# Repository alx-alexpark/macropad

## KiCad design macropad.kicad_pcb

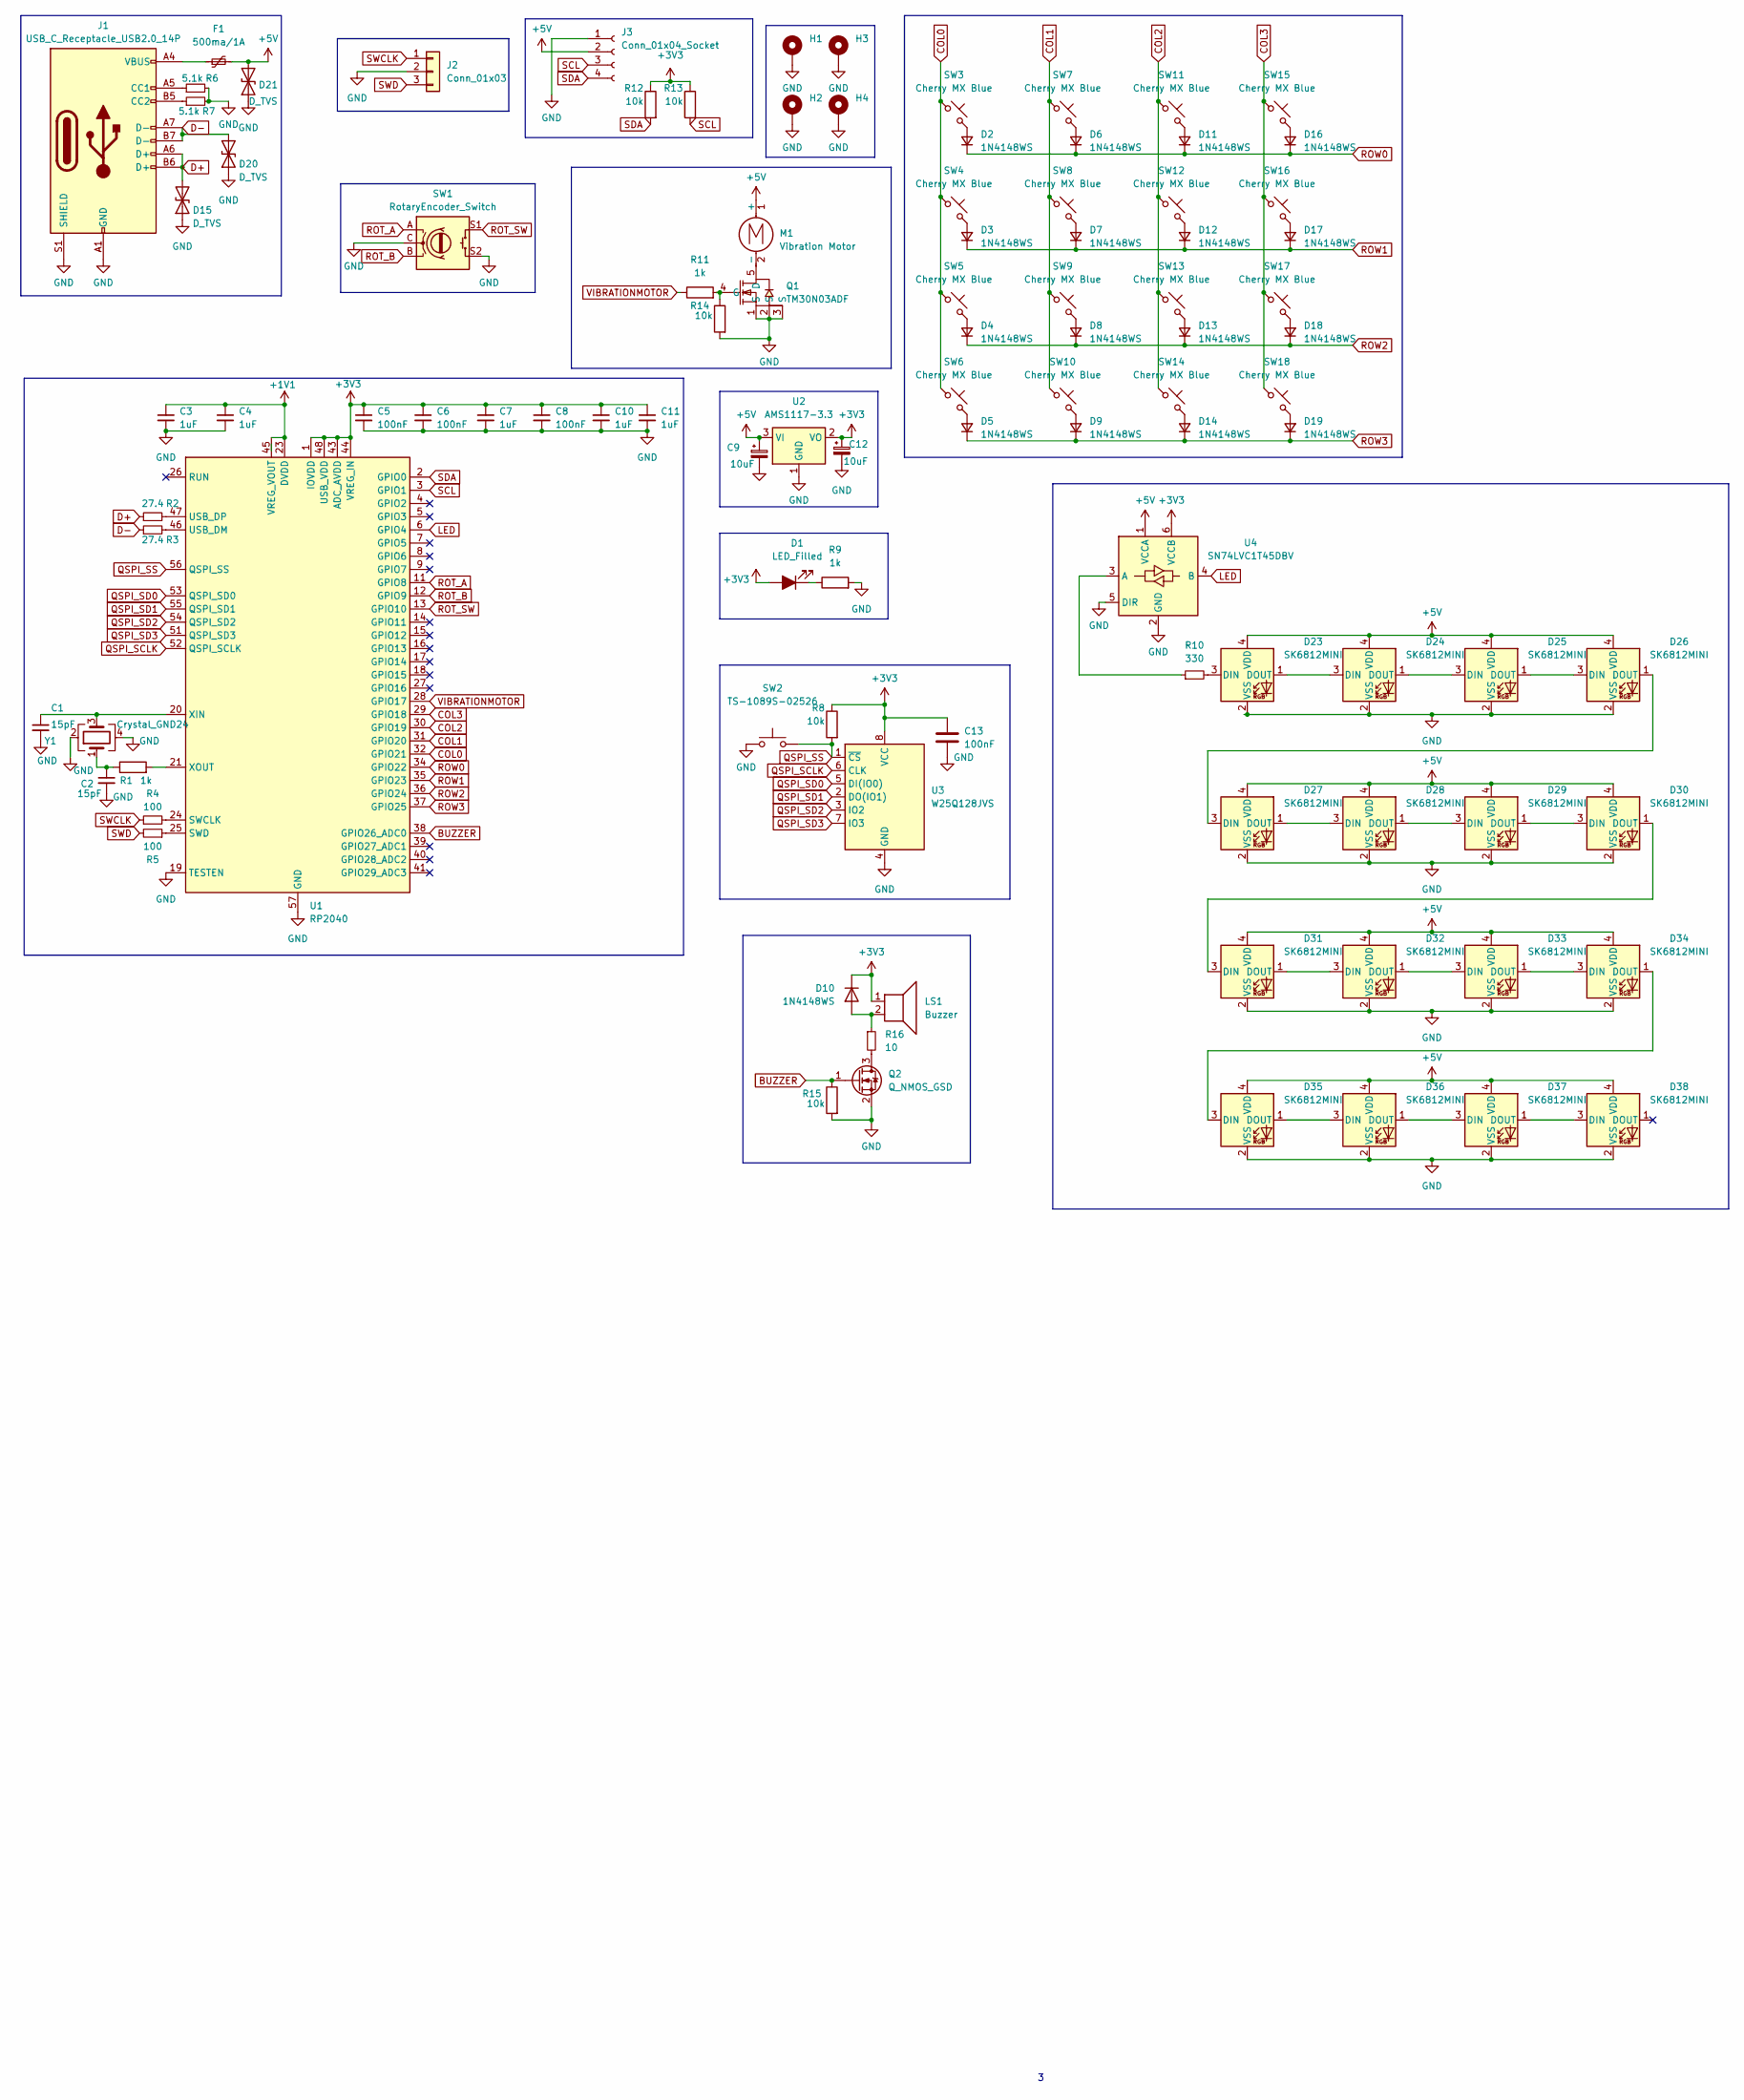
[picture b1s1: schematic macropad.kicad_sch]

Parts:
C1, C2: 15pF; C_0402_1005Metric; LCSC Part C1548
C3, C4, C7, C10, C11: 1uF; C_0402_1005Metric; LCSC Part C52923
C5, C6, C8, C13: 100nF; C_0402_1005Metric; LCSC Part C1525
C9, C12: 10uF; C_1206_3216Metric; LCSC Part C7171
D1: LED_Filled; LED_0603_1608Metric; LCSC Part C2286
D2, D3, D4, D5, D6, D7, D8, D9, D11, D12, D13, D14, D16, D17, D18, D19: 1N4148WS; D_SOD-323F; LCSC Part C917117
D10: 1N4148WS; D_SOD-323; LCSC Part C2828422
D15, D20, D21: D_TVS; D_SOD-923; LCSC Part C96512
D23, D24, D25, D26, D27, D28, D29, D30, D31, D32, D33, D34, D35, D36, D37, D38: SK6812MINI; SK6812MINI-E; LCSC Part C5149201
F1: 500ma/1A; Fuse_1206_3216Metric_Pad1.42x1.75mm_HandSolder; LCSC Part C720075
H1, H2, H3, H4: MountingHole_Pad; MountingHole_2.2mm_M2_DIN965_Pad
J1: USB_C_Receptacle_USB2.0_14P; USB_C_Receptacle_G-Switch_GT-USB-7010ASV; LCSC Part C2988369
J2: Conn_01x03; JST_SH_BM03B-SRSS-TB_1x03-1MP_P1.00mm_Vertical; LCSC Part C160389
J3: Conn_01x04_Socket; OLED-TH_L38.0-W12.0_HS91L02W2C01; LCSC Part C5248081
LS1: Buzzer; BUZ-SMD_4P-L8.5-W8.5-P8.50-BR; LCSC Part C94599
M1: Vibration Motor; PinHeader_1x02_P2.54mm_Vertical
Q1: TM30N03ADF; WDFN-5_L3.3-W3.3-P0.65-BL; LCSC Part C7422839
Q2: Q_NMOS_GSD; SOT-23_Handsoldering; LCSC Part C347475
R1, R9, R11: 1k; R_0402_1005Metric; LCSC Part C11702
R2, R3: 27.4; R_0603_1608Metric; LCSC Part C5126244
R4, R5: 100; R_0603_1608Metric_Pad0.98x0.95mm_HandSolder; LCSC Part C7250
R6, R7: 5.1k; R_0603_1608Metric_Pad0.98x0.95mm_HandSolder; LCSC Part C23186
R8, R12, R13, R14, R15: 10k; R_0805_2012Metric; LCSC Part C17414
R10: 330; R_0603_1608Metric_Pad0.98x0.95mm_HandSolder; LCSC Part C23138
R16: 10; R_0603_1608Metric_Pad0.98x0.95mm_HandSolder; LCSC Part C22859
SW1: RotaryEncoder_Switch; SW-TH_EC11XXXXXXXX; LCSC Part C470742
SW2: TS-1089S-02526; SW-SMD_4P-L4.2-W3.3-P2.15-LS5.1; LCSC Part C455282
SW3, SW4, SW5, SW6, SW7, SW8, SW9, SW10, SW11, SW12, SW13, SW14, SW15, SW16, SW17, SW18: Cherry MX Blue; SW_Cherry_MX_PCB_1.00u
U1: RP2040; QFN-56-1EP_7x7mm_P0.4mm_EP3.2x3.2mm; LCSC Part C2040
U2: AMS1117-3.3; SOT-223-3_TabPin2; LCSC Part C6186
U3: W25Q128JVS; SOIC-8_5.23x5.23mm_P1.27mm; LCSC Part C97521
U4: SN74LVC1T45DBV; SOT-23-6; LCSC Part C7843
Y1: Crystal_GND24; Crystal_SMD_3225-4Pin_3.2x2.5mm; LCSC Part C20625731

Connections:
+1V1: C3.1, C4.1, U1.23 (DVDD), U1.45 (VREG_VOUT), U1.50 (DVDD)
+3V3: C5.1, C6.1, C7.1, C8.1, C10.1, C11.1, C12.1, C13.1, D1.2 (A), D10.1 (K), LS1.1, R8.1, R12.1, R13.1, U1.1 (IOVDD), U1.10 (IOVDD), U1.22 (IOVDD), U1.33 (IOVDD), U1.42 (IOVDD), U1.43 (ADC_AVDD), U1.44 (VREG_IN), U1.48 (USB_VDD), U1.49 (IOVDD), U2.2 (VO), U3.8 (VCC), U4.6 (VCCB)
+5V: C9.1, D21.2 (A2), D23.4 (VDD), D24.4 (VDD), D25.4 (VDD), D26.4 (VDD), D27.4 (VDD), D28.4 (VDD), D29.4 (VDD), D30.4 (VDD), D31.4 (VDD), D32.4 (VDD), D33.4 (VDD), D34.4 (VDD), D35.4 (VDD), D36.4 (VDD), D37.4 (VDD), D38.4 (VDD), F1.2, J3.2, M1.1 (+), U2.3 (VI), U4.1 (VCCA)
BUZZER: Q2.1 (G), R15.1, U1.38 (GPIO26_ADC0)
COL0: SW3.1, SW4.1, SW5.1, SW6.1, U1.32 (GPIO21)
COL1: SW7.1, SW8.1, SW9.1, SW10.1, U1.31 (GPIO20)
COL2: SW11.1, SW12.1, SW13.1, SW14.1, U1.30 (GPIO19)
COL3: SW15.1, SW16.1, SW17.1, SW18.1, U1.29 (GPIO18)
D+: D15.2 (A2), J1.A6 (D+), J1.B6 (D+), R2.1
D-: D20.2 (A2), J1.A7 (D-), J1.B7 (D-), R3.1
GND: C1.2, C2.2, C3.2, C4.2, C5.2, C6.2, C7.2, C8.2, C9.2, C10.2, C11.2, C12.2, C13.2, D15.1 (A1), D20.1 (A1), D21.1 (A1), D23.2 (VSS), D24.2 (VSS), D25.2 (VSS), D26.2 (VSS), D27.2 (VSS), D28.2 (VSS), D29.2 (VSS), D30.2 (VSS), D31.2 (VSS), D32.2 (VSS), D33.2 (VSS), D34.2 (VSS), D35.2 (VSS), D36.2 (VSS), D37.2 (VSS), D38.2 (VSS), H1.1, H2.1, H3.1, H4.1, J1.A1 (GND), J1.A12 (GND), J1.B1 (GND), J1.B12 (GND), J1.S1 (SHIELD), J2.2, J3.1, Q1.1 (S), Q1.2 (S), Q1.3 (S), Q2.2 (S), R6.2, R7.2, R9.2, R14.2, R15.2, SW1.C, SW1.S2, SW2.1, U1.19 (TESTEN), U1.57 (GND), U2.1 (GND), U3.4 (GND), U4.2 (GND), U4.5 (DIR), Y1.2, Y1.4
LED: U1.6 (GPIO4), U4.4 (B)
unnamed: C2.1, R1.1, Y1.1
unnamed: D1.1 (K), R9.1
unnamed: D2.2 (A), SW3.2
unnamed: D3.2 (A), SW4.2
unnamed: D4.2 (A), SW5.2
unnamed: D5.2 (A), SW6.2
unnamed: D6.2 (A), SW7.2
unnamed: D7.2 (A), SW8.2
unnamed: D8.2 (A), SW9.2
unnamed: D9.2 (A), SW10.2
unnamed: D10.2 (A), LS1.2, R16.1
unnamed: D11.2 (A), SW11.2
unnamed: D12.2 (A), SW12.2
unnamed: D13.2 (A), SW13.2
unnamed: D14.2 (A), SW14.2
unnamed: D16.2 (A), SW15.2
unnamed: D17.2 (A), SW16.2
unnamed: D18.2 (A), SW17.2
unnamed: D19.2 (A), SW18.2
unnamed: D23.3 (DIN), R10.2
unnamed: D23.1 (DOUT), D24.3 (DIN)
unnamed: D24.1 (DOUT), D25.3 (DIN)
unnamed: D25.1 (DOUT), D26.3 (DIN)
unnamed: D26.1 (DOUT), D27.3 (DIN)
unnamed: D27.1 (DOUT), D28.3 (DIN)
unnamed: D28.1 (DOUT), D29.3 (DIN)
unnamed: D29.1 (DOUT), D30.3 (DIN)
unnamed: D30.1 (DOUT), D31.3 (DIN)
unnamed: D31.1 (DOUT), D32.3 (DIN)
unnamed: D32.1 (DOUT), D33.3 (DIN)
unnamed: D33.1 (DOUT), D34.3 (DIN)
unnamed: D34.1 (DOUT), D35.3 (DIN)
unnamed: D35.1 (DOUT), D36.3 (DIN)
unnamed: D36.1 (DOUT), D37.3 (DIN)
unnamed: D37.1 (DOUT), D38.3 (DIN)
unnamed: F1.1, J1.A4 (VBUS), J1.A9 (VBUS), J1.B4 (VBUS), J1.B9 (VBUS)
unnamed: J1.A5 (CC1), R6.1
unnamed: J1.B5 (CC2), R7.1
unnamed: M1.2 (-), Q1.5 (D)
unnamed: Q1.4 (G), R11.2, R14.1
unnamed: Q2.3 (D), R16.2
unnamed: R4.2, U1.24 (SWCLK)
unnamed: R5.1, U1.25 (SWD)
unnamed: R3.2, U1.46 (USB_DM)
unnamed: R2.2, U1.47 (USB_DP)
unnamed: C1.1, U1.20 (XIN), Y1.3
unnamed: R1.2, U1.21 (XOUT)
unnamed: R10.1, U4.3 (A)
QSPI_SCLK: U1.52 (QSPI_SCLK), U3.6 (CLK)
QSPI_SD0: U1.53 (QSPI_SD0), U3.5 (DI(IO0))
QSPI_SD1: U1.55 (QSPI_SD1), U3.2 (DO(IO1))
QSPI_SD2: U1.54 (QSPI_SD2), U3.3 (IO2)
QSPI_SD3: U1.51 (QSPI_SD3), U3.7 (IO3)
QSPI_SS: R8.2, SW2.2, U1.56 (QSPI_SS), U3.1 (~CS)
ROT_A: SW1.A, U1.11 (GPIO8)
ROT_B: SW1.B, U1.12 (GPIO9)
ROT_SW: SW1.S1, U1.13 (GPIO10)
ROW0: D2.1 (K), D6.1 (K), D11.1 (K), D16.1 (K), U1.34 (GPIO22)
ROW1: D3.1 (K), D7.1 (K), D12.1 (K), D17.1 (K), U1.35 (GPIO23)
ROW2: D4.1 (K), D8.1 (K), D13.1 (K), D18.1 (K), U1.36 (GPIO24)
ROW3: D5.1 (K), D9.1 (K), D14.1 (K), D19.1 (K), U1.37 (GPIO25)
SCL: J3.3, R13.2, U1.3 (GPIO1)
SDA: J3.4, R12.2, U1.2 (GPIO0)
SWCLK: J2.1, R4.1
SWD: J2.3, R5.2
VIBRATIONMOTOR: R11.1, U1.28 (GPIO17)

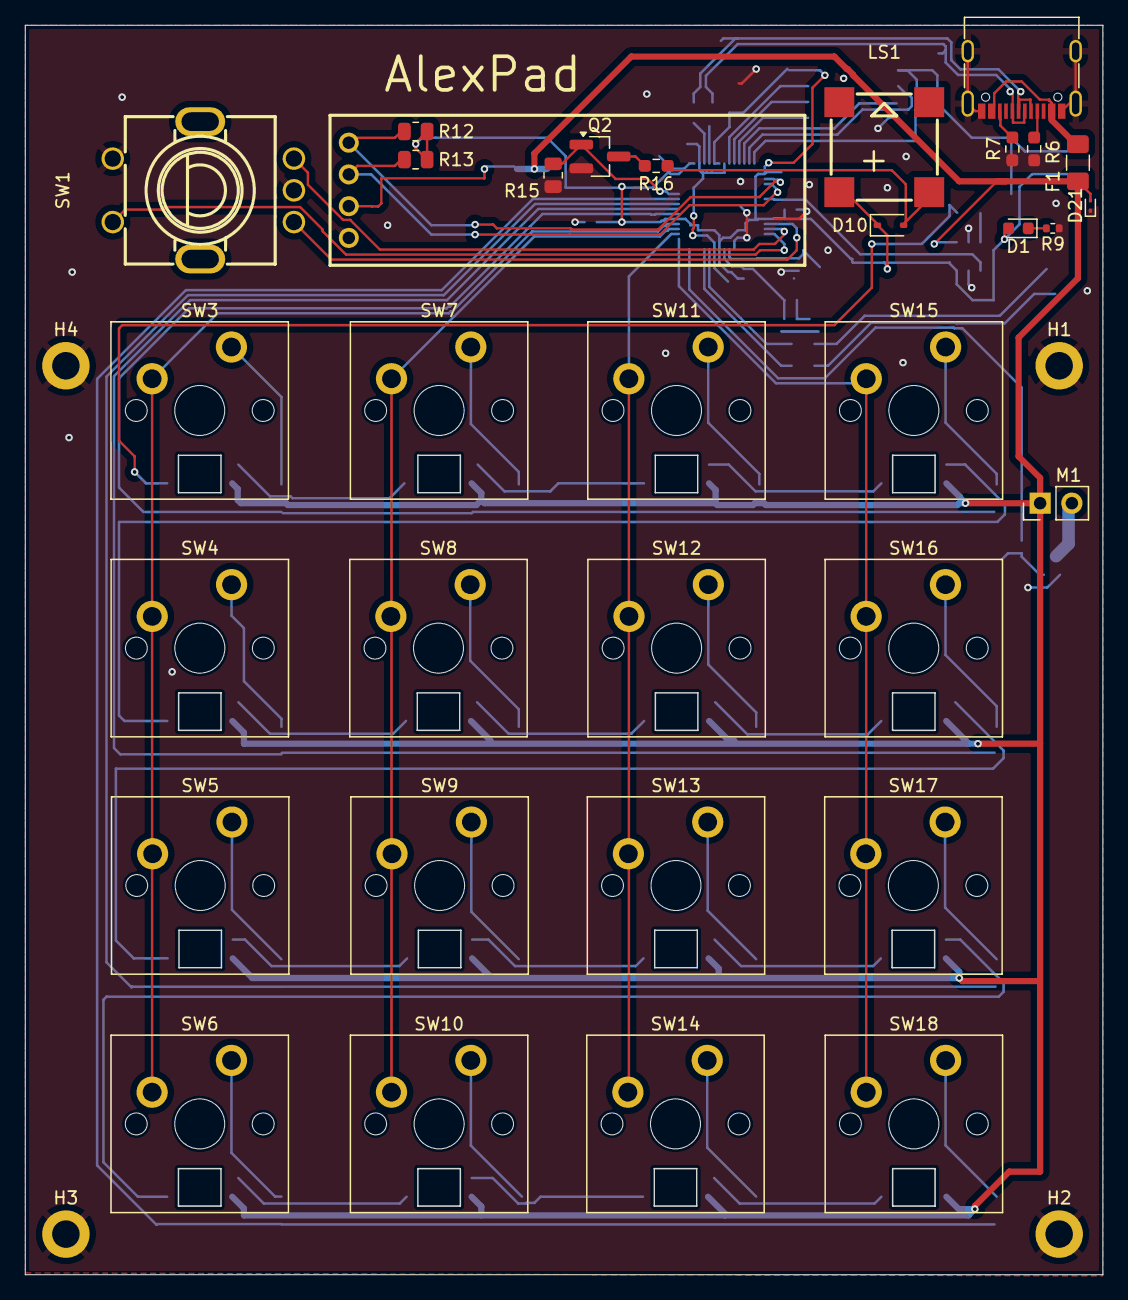
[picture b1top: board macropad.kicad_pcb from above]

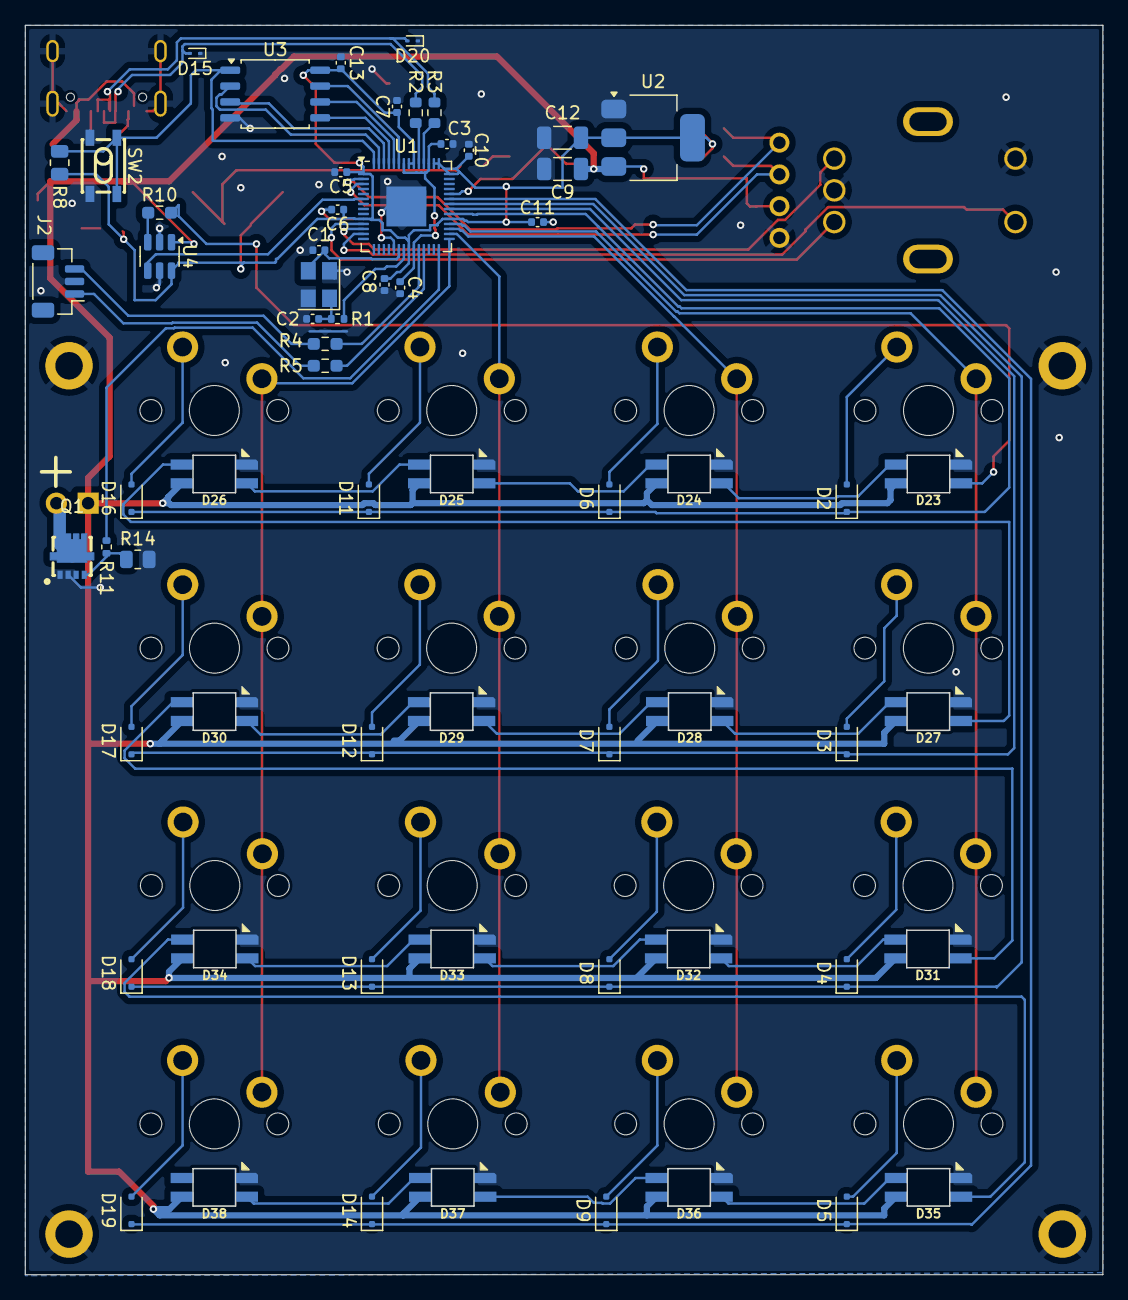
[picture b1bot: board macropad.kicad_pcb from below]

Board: 2 copper layers, 86.2 x 100.0 mm, 101 parts (64 on the bottom side), 78 nets.

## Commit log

2025-01-28 Change MCU
2025-01-31 did some layout things
2025-02-02 Commit before upgrading to 9rc-2
2025-02-10 I did things
2025-02-16 save things before kicad breaks stuff
2025-02-16 almost done
2025-03-19 Final product: version 1
